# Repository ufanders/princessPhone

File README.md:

# princessPhone

TL;DR: Bluetooth adaptor for standard wired telephones. Just plug it in.

This project bridges the gap between the wired telephones we grew up with and our modern (mobile) telephones. Contains a PIC32MX1 microcontroller, RN-52 Bluetooth audio module, Silvertel AG1170 SLIC and audio support components.

=]

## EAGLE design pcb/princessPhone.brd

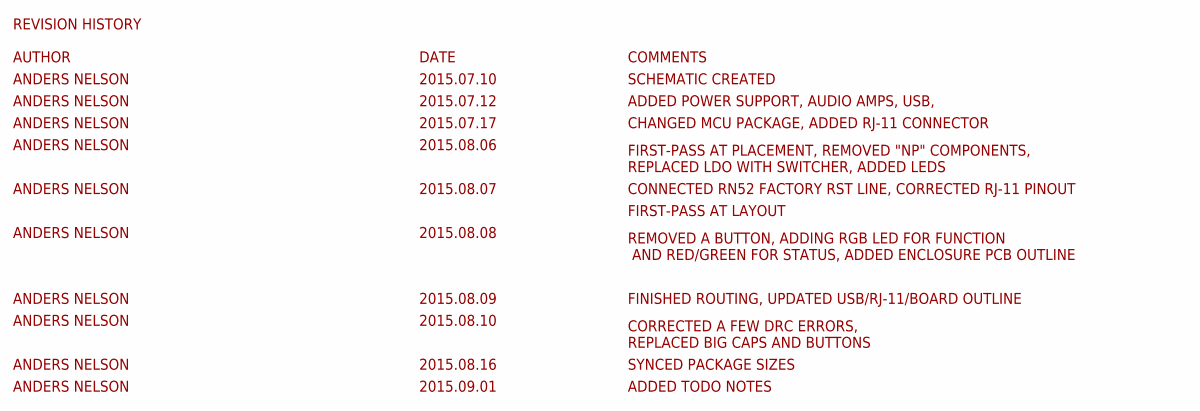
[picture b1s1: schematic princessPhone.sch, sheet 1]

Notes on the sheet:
REVISION HISTORY
AUTHOR
DATE
COMMENTS
ANDERS NELSON
2015.07.10
SCHEMATIC CREATED
2015.07.12
ADDED POWER SUPPORT, AUDIO AMPS, USB,
2015.07.17
CHANGED MCU PACKAGE, ADDED RJ-11 CONNECTOR
2015.08.06
FIRST-PASS AT PLACEMENT, REMOVED "NP" COMPONENTS, REPLACED LDO WITH SWITCHER, ADDED LEDS
2015.08.07
CONNECTED RN52 FACTORY RST LINE, CORRECTED RJ-11 PINOUT
FIRST-PASS AT LAYOUT
2015.08.08
REMOVED A BUTTON, ADDING RGB LED FOR FUNCTION AND RED/GREEN FOR STATUS, ADDED ENCLOSURE PCB OUTLINE
2015.08.09
FINISHED ROUTING, UPDATED USB/RJ-11/BOARD OUTLINE
2015.08.10
CORRECTED A FEW DRC ERRORS, REPLACED BIG CAPS AND BUTTONS
2015.08.16
SYNCED PACKAGE SIZES
2015.09.01
ADDED TODO NOTES

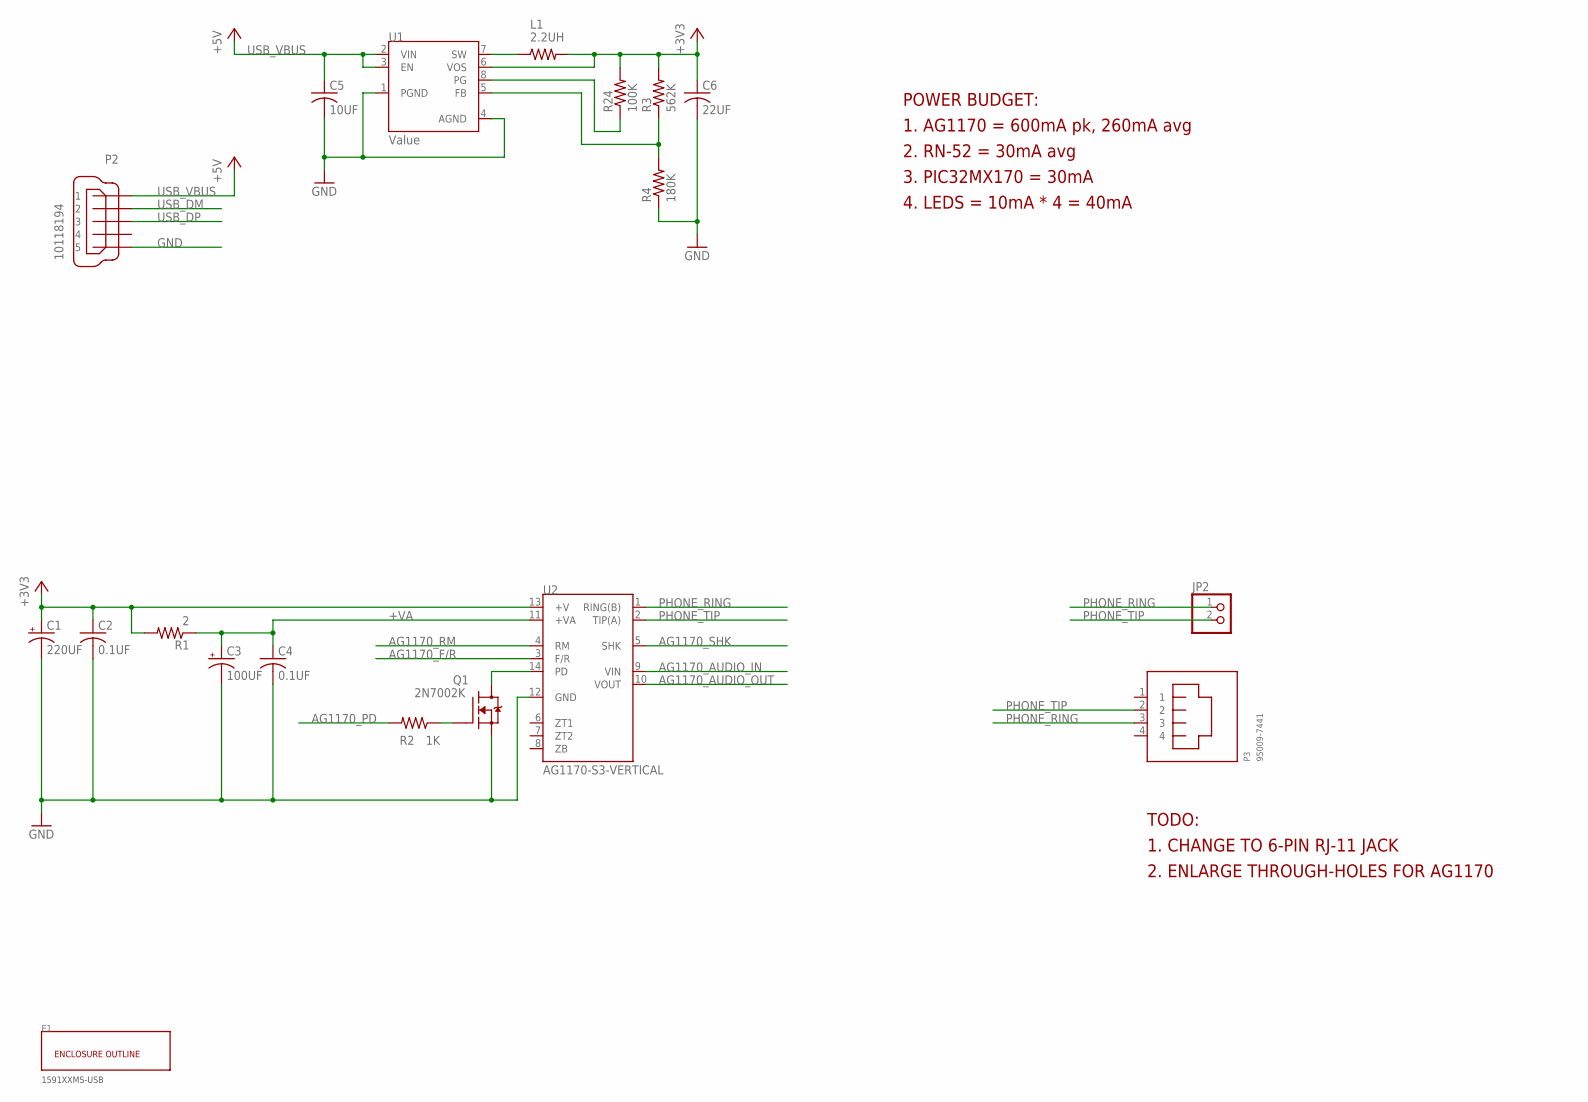
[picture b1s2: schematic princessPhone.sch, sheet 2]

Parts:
C1: 220UF; E2,5-7
C2, C4: 0.1UF; C0603
C3: 100UF; E2,5-7
C5: 10UF; C0603
C6: 22UF; C1206
E1: 1591XXMS-USB; 1591XXMSBK-USB
JP2: PINHD-1X2; 1X02
L1: 2.2UH; R0805
P2: 10118194
P3: 95009-7441
Q1: 2N7002K; SOT23
R1: 2; R0603
R2: 1K; R0603
R3: 562K; R0603
R4: 180K; R0603
R24: 100K; R0603
U1: Value; DGK0008A_N
U2: AG1170-S3-VERTICAL; AG1170X-S

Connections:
+3V3: C1.+, C2.1, C6.1, L1.2, R1.2, R3.2, R24.2, U1.6 (VOS), U2.13 (+V); also elsewhere on the board
+VA: C3.+, C4.1, R1.1, U2.11 (+VA)
AG1170_AUDIO_IN: U2.9 (VIN); also elsewhere on the board
AG1170_AUDIO_OUT: U2.10 (VOUT); also elsewhere on the board
AG1170_F/R: U2.3 (F/R); also elsewhere on the board
AG1170_PD: R2.2; also elsewhere on the board
AG1170_RM: U2.4 (RM); also elsewhere on the board
AG1170_SHK: U2.5 (SHK); also elsewhere on the board
GND: C1.-, C2.2, C3.-, C4.2, C5.2, C6.2, P2.5, Q1.2 (S), R4.1, U1.1 (PGND), U1.4 (AGND), U2.12 (GND); also elsewhere on the board
unnamed: Q1.1 (G), R2.1
unnamed: Q1.3 (D), U2.14 (PD)
unnamed: L1.1, U1.7 (SW)
unnamed: R24.1, U1.8 (PG)
unnamed: R3.1, R4.2, U1.5 (FB)
PHONE_RING: JP2.1, P3.3, U2.1 (RING(B))
PHONE_TIP: JP2.2, P3.2, U2.2 (TIP(A))
USB_DM: P2.2; also elsewhere on the board
USB_DP: P2.3; also elsewhere on the board
USB_VBUS: C5.1, P2.1, U1.2 (VIN), U1.3 (EN); also elsewhere on the board

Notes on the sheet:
POWER BUDGET:
1. AG1170 = 600mA pk, 260mA avg
2. RN-52 = 30mA avg
3. PIC32MX170 = 30mA
4. LEDS = 10mA * 4 = 40mA
TODO:
1. CHANGE TO 6-PIN RJ-11 JACK
2. ENLARGE THROUGH-HOLES FOR AG1170

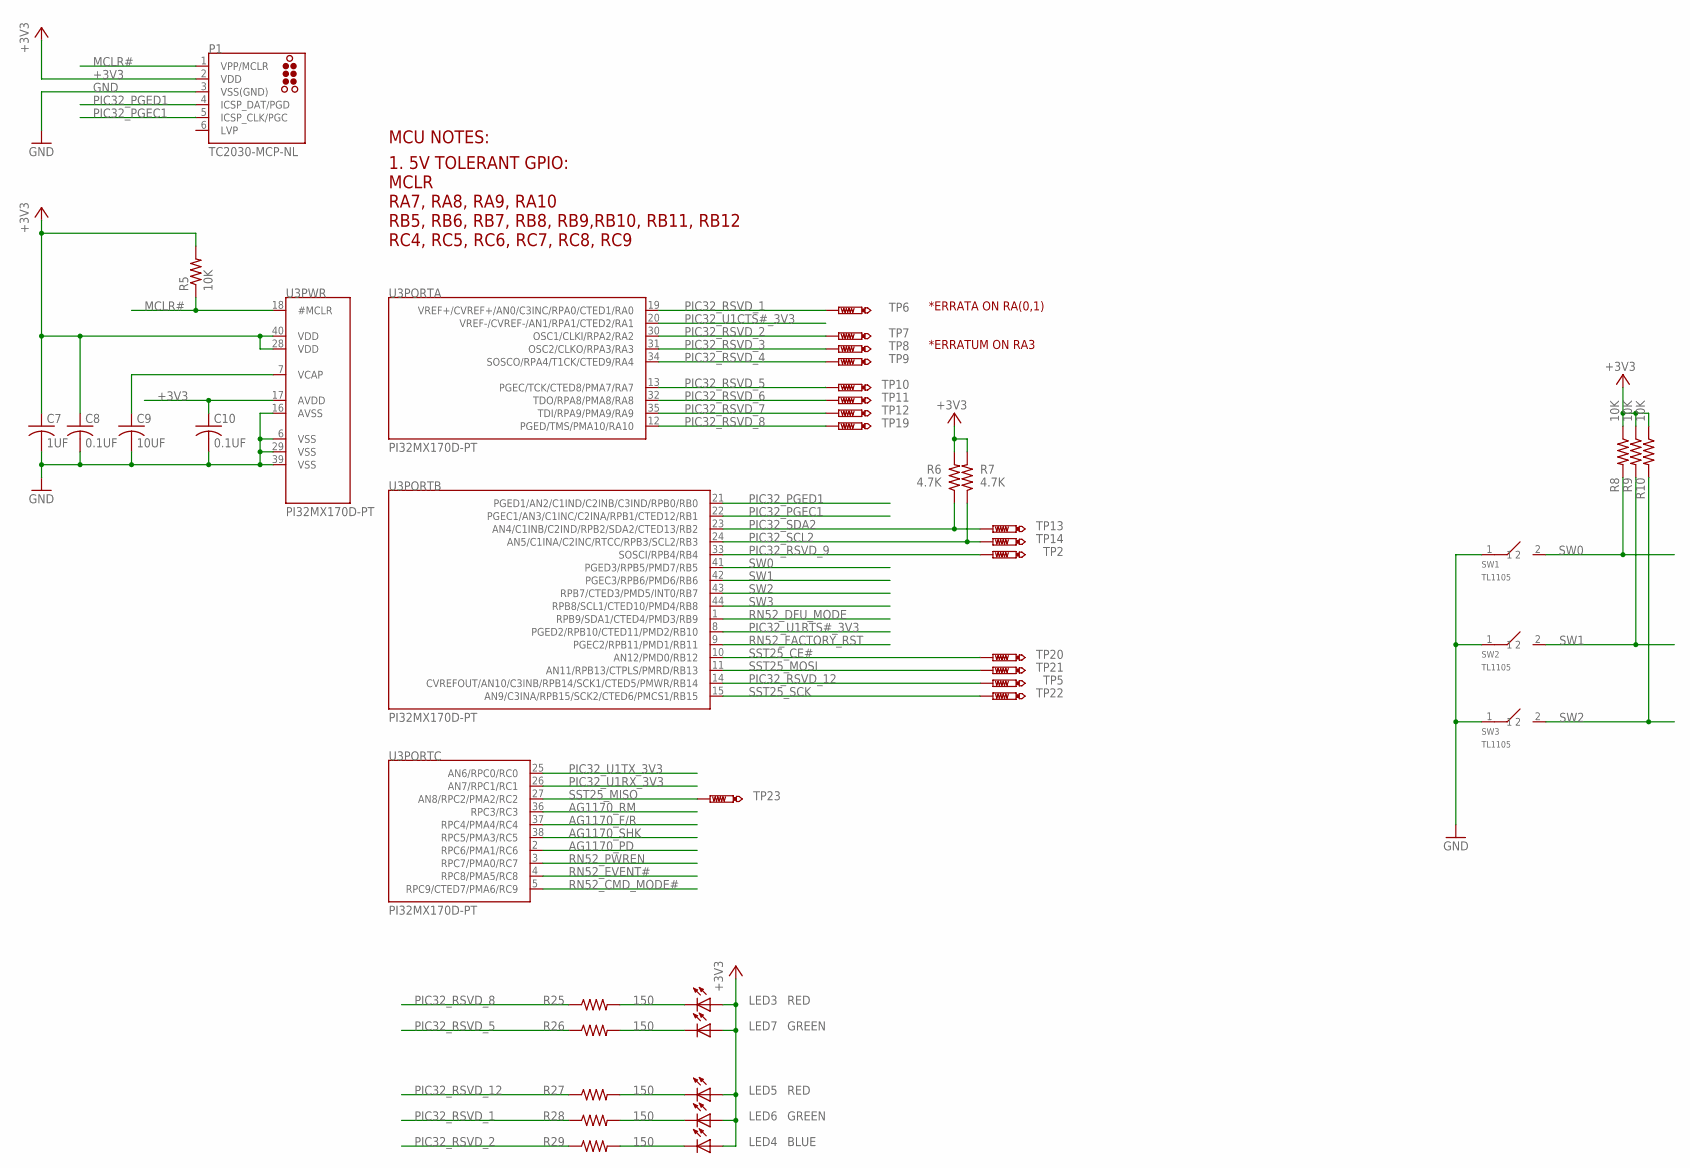
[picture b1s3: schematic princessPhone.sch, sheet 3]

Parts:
C7: 1UF; C0603
C8, C10: 0.1UF; C0603
C9: 10UF; C0603
LED3, LED5: RED; CHIPLED_0603
LED4: BLUE; CHIPLED_0603
LED6, LED7: GREEN; CHIPLED_0603
P1: TC2030-MCP-NL
R5, R8, R9, R10: 10K; R0603
R6, R7: 4.7K; R0603
R25, R26, R27, R28, R29: 150; R0603
SW1, SW2, SW3: TL1105; TL1105_RA
TP2, TP5, TP6, TP7, TP8, TP9, TP10, TP11, TP12, TP13, TP14, TP19, TP20, TP21, TP22, TP23: PTR1B1,27; B1,27
U3: PI32MX170D-PT; TQFP44

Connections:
+3V3: C7.1, C8.1, C10.1, LED3.A, LED4.A, LED5.A, LED6.A, LED7.A, P1.2 (VDD), R5.2, R6.2, R7.2, R8.1, R9.1, R10.1, U3.17 (AVDD), U3.28 (VDD), U3.40 (VDD); also elsewhere on the board
AG1170_F/R: U3.37 (RPC4/PMA4/RC4); also elsewhere on the board
AG1170_PD: U3.2 (RPC6/PMA1/RC6); also elsewhere on the board
AG1170_RM: U3.36 (RPC3/RC3); also elsewhere on the board
AG1170_SHK: U3.38 (RPC5/PMA3/RC5); also elsewhere on the board
GND: C7.2, C8.2, C9.2, C10.2, P1.3 (VSS(GND)), SW1.1, SW2.1, SW3.1, U3.6 (VSS), U3.16 (AVSS), U3.29 (VSS), U3.39 (VSS); also elsewhere on the board
MCLR#: P1.1 (VPP/MCLR), R5.1, U3.18 (#MCLR)
unnamed: LED5.C, R27.2
unnamed: C9.1, U3.7 (VCAP)
unnamed: LED3.C, R25.2
unnamed: LED7.C, R26.2
unnamed: LED6.C, R28.2
unnamed: LED4.C, R29.2
PIC32_PGEC1: P1.5 (ICSP_CLK/PGC), U3.22 (PGEC1/AN3/C1INC/C2INA/RPB1/CTED12/RB1)
PIC32_PGED1: P1.4 (ICSP_DAT/PGD), U3.21 (PGED1/AN2/C1IND/C2INB/C3IND/RPB0/RB0)
PIC32_RSVD_1: R28.1, TP6.TP, U3.19 (VREF+/CVREF+/AN0/C3INC/RPA0/CTED1/RA0)
PIC32_RSVD_2: R29.1, TP7.TP, U3.30 (OSC1/CLKI/RPA2/RA2)
PIC32_RSVD_3: TP8.TP, U3.31 (OSC2/CLKO/RPA3/RA3)
PIC32_RSVD_4: TP9.TP, U3.34 (SOSCO/RPA4/T1CK/CTED9/RA4)
PIC32_RSVD_5: R26.1, TP10.TP, U3.13 (PGEC/TCK/CTED8/PMA7/RA7)
PIC32_RSVD_6: TP11.TP, U3.32 (TDO/RPA8/PMA8/RA8)
PIC32_RSVD_7: TP12.TP, U3.35 (TDI/RPA9/PMA9/RA9)
PIC32_RSVD_8: R25.1, TP19.TP, U3.12 (PGED/TMS/PMA10/RA10)
PIC32_RSVD_9: TP2.TP, U3.33 (SOSCI/RPB4/RB4)
PIC32_RSVD_12: R27.1, TP5.TP, U3.14 (CVREFOUT/AN10/C3INB/RPB14/SCK1/CTED5/PM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)
PIC32_SCL2: R7.1, TP14.TP, U3.24 (AN5/C1INA/C2INC/RTCC/RPB3/SCL2/RB3)
PIC32_SDA2: R6.1, TP13.TP, U3.23 (AN4/C1INB/C2IND/RPB2/SDA2/CTED13/RB2)
PIC32_U1CTS#_3V3: U3.20 (VREF-/CVREF-/AN1/RPA1/CTED2/RA1); also elsewhere on the board
PIC32_U1RTS#_3V3: U3.8 (PGED2/RPB10/CTED11/PMD2/RB10); also elsewhere on the board
PIC32_U1RX_3V3: U3.26 (AN7/RPC1/RC1); also elsewhere on the board
PIC32_U1TX_3V3: U3.25 (AN6/RPC0/RC0); also elsewhere on the board
RN52_CMD_MODE#: U3.5 (RPC9/CTED7/PMA6/RC9); also elsewhere on the board
RN52_DFU_MODE: U3.1 (RPB9/SDA1/CTED4/PMD3/RB9); also elsewhere on the board
RN52_EVENT#: U3.4 (RPC8/PMA5/RC8); also elsewhere on the board
RN52_FACTORY_RST: U3.9 (PGEC2/RPB11/PMD1/RB11); also elsewhere on the board
RN52_PWREN: U3.3 (RPC7/PMA0/RC7); also elsewhere on the board
SST25_CE#: TP20.TP, U3.10 (AN12/PMD0/RB12)
SST25_MISO: TP23.TP, U3.27 (AN8/RPC2/PMA2/RC2)
SST25_MOSI: TP21.TP, U3.11 (AN11/RPB13/CTPLS/PMRD/RB13)
SST25_SCK: TP22.TP, U3.15 (AN9/C3INA/RPB15/SCK2/CTED6/PMCS1/RB15)
SW0: R8.2, SW1.2, U3.41 (PGED3/RPB5/PMD7/RB5)
SW1: R9.2, SW2.2, U3.42 (PGEC3/RPB6/PMD6/RB6)
SW2: R10.2, SW3.2, U3.43 (RPB7/CTED3/PMD5/INT0/RB7)
SW3: U3.44 (RPB8/SCL1/CTED10/PMD4/RB8)

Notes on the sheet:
*ERRATUM ON RA3
1. 5V TOLERANT GPIO: MCLR RA7, RA8, RA9, RA10 RB5, RB6, RB7, RB8, RB9,RB10, RB11, RB12 RC4, RC5, RC6, RC7, RC8, RC9
*ERRATA ON RA(0,1)
MCU NOTES:

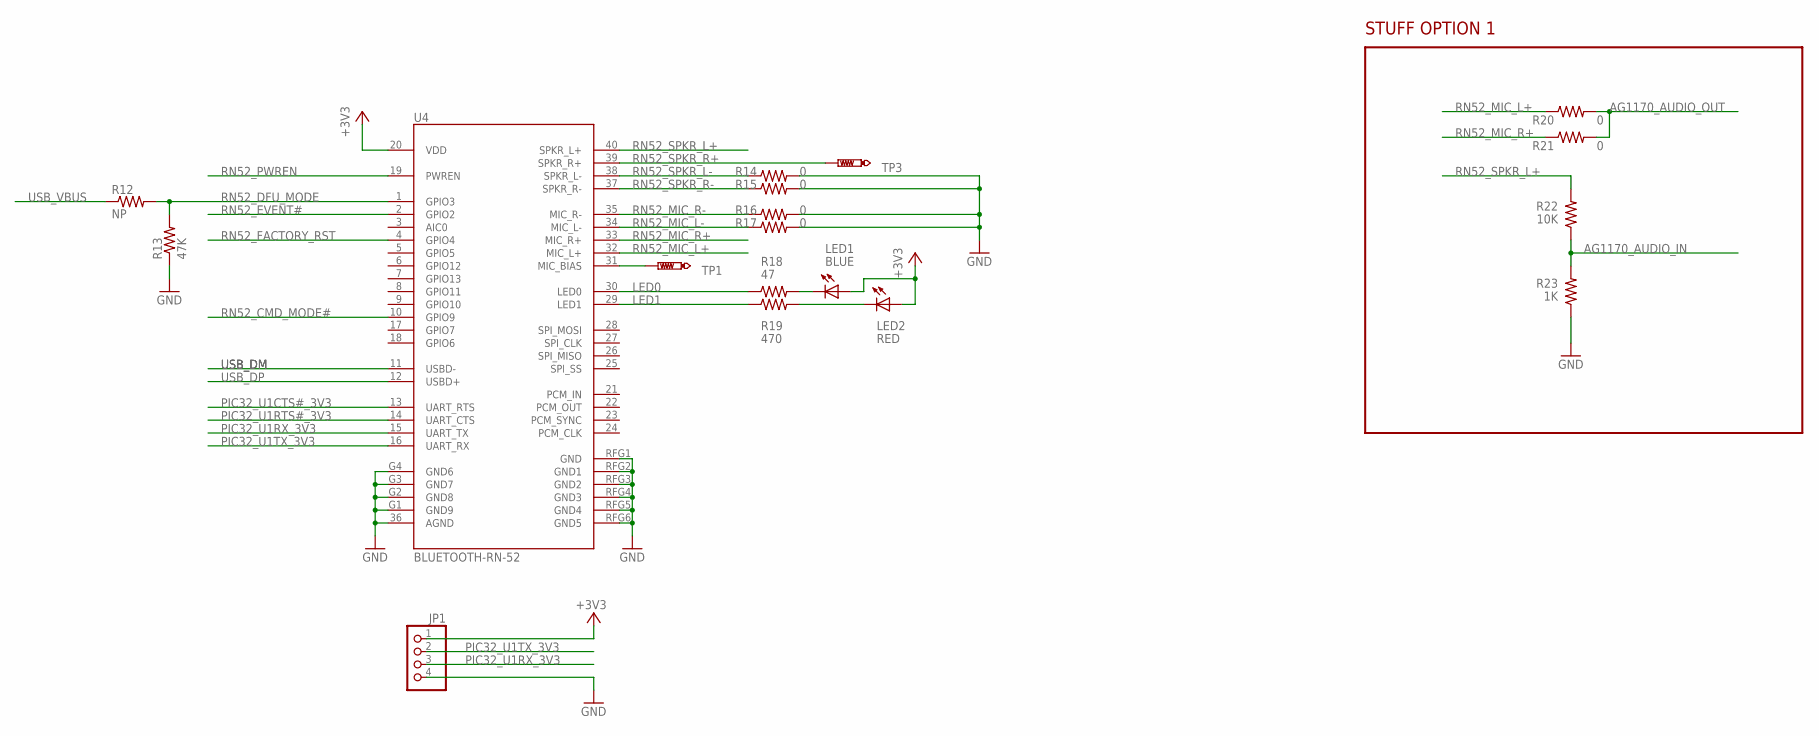
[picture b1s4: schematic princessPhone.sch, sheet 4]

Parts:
JP1: PINHD-1X4; 1X04
LED1: BLUE; CHIPLED_0603
LED2: RED; CHIPLED_0603
R12: NP; R0603
R13: 47K; R0603
R14, R15, R16, R17, R20, R21: 0; R0603
R18: 47; R0603
R19: 470; R0603
R22: 10K; R0603
R23: 1K; R0603
TP1, TP3: PTR1B1,27; B1,27
U4: BLUETOOTH-RN-52; RN-52

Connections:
+3V3: JP1.1, LED1.A, LED2.A, U4.20 (VDD); also elsewhere on the board
AG1170_AUDIO_IN: R22.1, R23.2; also elsewhere on the board
AG1170_AUDIO_OUT: R20.2, R21.2; also elsewhere on the board
GND: JP1.4, R13.1, R14.2, R15.2, R16.2, R17.2, R23.1, U4.36 (AGND), U4.G1 (GND9), U4.G2 (GND8), U4.G3 (GND7), U4.G4 (GND6), U4.RFG1 (GND), U4.RFG2 (GND1), U4.RFG3 (GND2), U4.RFG4 (GND3), U4.RFG5 (GND4), U4.RFG6 (GND5); also elsewhere on the board
LED0: R18.1, U4.30 (LED0)
LED1: R19.1, U4.29 (LED1)
unnamed: LED1.C, R18.2
unnamed: LED2.C, R19.2
unnamed: TP1.TP, U4.31 (MIC_BIAS)
PIC32_U1CTS#_3V3: U4.13 (UART_RTS); also elsewhere on the board
PIC32_U1RTS#_3V3: U4.14 (UART_CTS); also elsewhere on the board
PIC32_U1RX_3V3: JP1.3, U4.15 (UART_TX); also elsewhere on the board
PIC32_U1TX_3V3: JP1.2, U4.16 (UART_RX); also elsewhere on the board
RN52_CMD_MODE#: U4.10 (GPIO9); also elsewhere on the board
RN52_DFU_MODE: R12.2, R13.2, U4.1 (GPIO3); also elsewhere on the board
RN52_EVENT#: U4.2 (GPIO2); also elsewhere on the board
RN52_FACTORY_RST: U4.4 (GPIO4); also elsewhere on the board
RN52_MIC_L+: R20.1, U4.32 (MIC_L+)
RN52_MIC_L-: R17.1, U4.34 (MIC_L-)
RN52_MIC_R+: R21.1, U4.33 (MIC_R+)
RN52_MIC_R-: R16.1, U4.35 (MIC_R-)
RN52_PWREN: U4.19 (PWREN); also elsewhere on the board
RN52_SPKR_L+: R22.2, U4.40 (SPKR_L+)
RN52_SPKR_L-: R14.1, U4.38 (SPKR_L-)
RN52_SPKR_R+: TP3.TP, U4.39 (SPKR_R+)
RN52_SPKR_R-: R15.1, U4.37 (SPKR_R-)
USB_DM: U4.11 (USBD-); also elsewhere on the board
USB_DP: U4.12 (USBD+); also elsewhere on the board
USB_VBUS: R12.1; also elsewhere on the board

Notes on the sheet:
STUFF OPTION 1

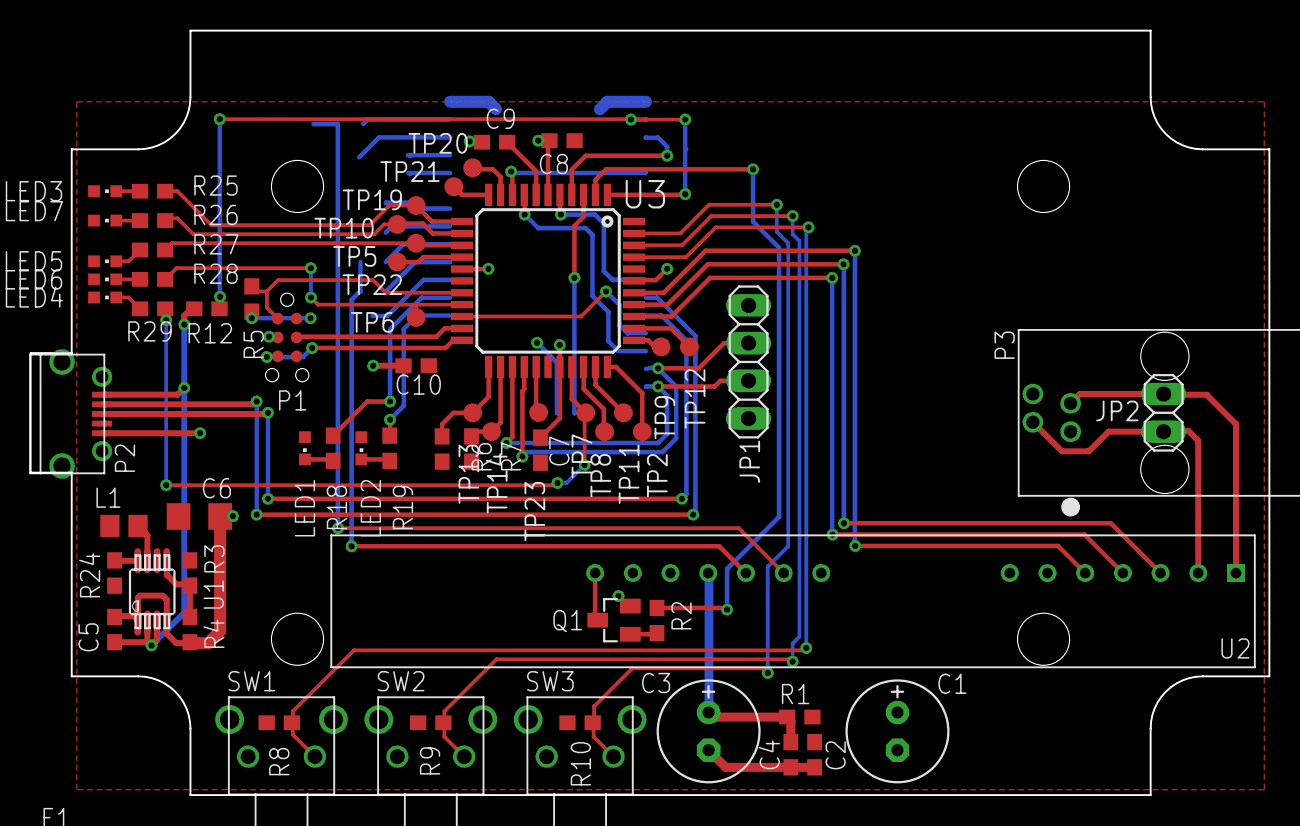
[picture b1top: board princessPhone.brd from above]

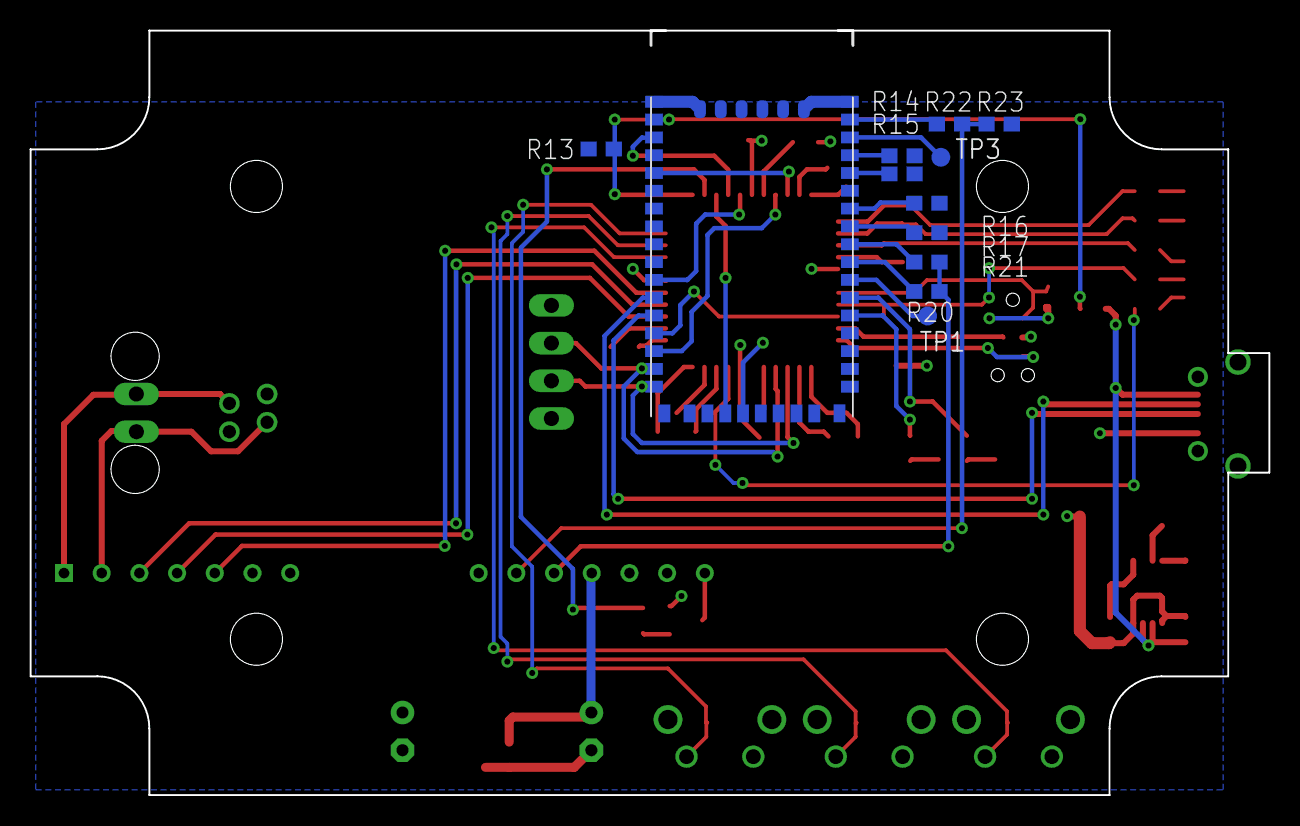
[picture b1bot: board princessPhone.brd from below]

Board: 2 copper layers, 83.5 x 51.5 mm, 78 parts (12 on the bottom side), 69 nets.

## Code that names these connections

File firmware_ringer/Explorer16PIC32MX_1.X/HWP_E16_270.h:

#ifndef HWP_E16_270_H
#define HWP_E16_270_H

#define VERSION_HARDWARE_MAJOR 'E'
#define VERSION_HARDWARE_MINOR 16

// Set configuration fuses (but only in Main.c where SET_CONFIG_FUSES is defined)
#if defined(SET_CONFIG_FUSES)

    //PROVIDES 48MHZ FCY
    #pragma config FPLLMUL  = MUL_24        // PLL Multiplier
    #pragma config FPLLIDIV = DIV_2          // PLL Input Divider
    #pragma config FPLLODIV = DIV_2     // PLL Output Divider
    #pragma config FPBDIV   = DIV_1         // Peripheral Clock divisor
    #pragma config WDTPS    = PS1           // Watchdog Timer Postscale
    #pragma config FCKSM    = CSDCMD        // Clock Switching & Fail Safe Clock Monitor
    #pragma config OSCIOFNC = OFF           // CLKO Enable
    #pragma config POSCMOD  = HS            // Primary Oscillator
    #pragma config IESO     = OFF           // Internal/External Switch-over
    #pragma config FSOSCEN  = ON           // Secondary Oscillator Enable
    #pragma config FNOSC    = PRIPLL        // Oscillator Selection

    #ifdef __DEBUG
        #pragma config CP       = OFF       // Code Protect
        #pragma config FWDTEN   = OFF       // Watchdog Timer
    #else
        #pragma config CP       = OFF        // Code Protect
        #pragma config FWDTEN   = OFF        // Watchdog Timer
    #endif

    #pragma config BWP      = OFF           // Boot Flash Write Protect
    #pragma config PWP      = OFF           // Program Flash Write Protect
    #pragma config ICESEL   = ICS_PGx2      // ICE/ICD Comm Channel Select
    #pragma config DEBUG    = ON            // Background Debugger Enable
    #pragma config FUSBIDIO = OFF
    #pragma config FVBUSONIO = OFF

#endif

// Clock frequency values
// These directly influence timed events using the Tick module.  They also are used for UART and SPI baud rate generation.
#define GetSystemClock()	(48000000ul)		// Hz
#define GetInstructionClock()	(GetSystemClock()/1)	// Normally GetSystemClock()/4 for PIC18, GetSystemClock()/2 for PIC24/dsPIC, and GetSystemClock()/1 for PIC32.  Might need changing if using Doze modes.
#define GetPeripheralClock()	(GetSystemClock()/1)	// Normally GetSystemClock()/4 for PIC18, GetSystemClock()/2 for PIC24/dsPIC, and GetSystemClock()/1 for PIC32.  Divisor may be different if using a PIC32 since it's configurable.
#define SYS_FREQ GetSystemClock()
#define PB_DIV 1

// Hardware I/O pin mappings
//UART
#define UART_RX_TRIS TRISCbits.TRISC1 //RB10 on riser card
#define UART_TX_TRIS TRISCbits.TRISC0 //RB11 on riser card
#define UART_RTS_TRIS TRISBbits.TRISB10 //RGO on riser card
#define UART_CTS_TRIS TRISAbits.TRISA1 //RE6on riser card
#define UART_RX_PPS 0b0110
#define UART_TX_PPS 0b0001
#define UART_RTS_PPS 0b0010
#define UART_CTS_PPS 0b0000

//AG1170 CONTROL LINES
#define AG1170_RM_TRIS TRISCbits.TRISC3 //RG13 on riser card
#define AG1170_FR_TRIS TRISCbits.TRISC4 //RG14 on riser card
#define AG1170_SHK_TRIS TRISCbits.TRISC5 //RG15 on riser card
#define AG1170_PD_TRIS TRISCbits.TRISC6
#define AG1170_RM_LAT LATCbits.LATC3 //RG13 on riser card
#define AG1170_FR_LAT LATCbits.LATC4 //RG14 on riser card
#define AG1170_SHK_LAT LATCbits.LATC5 //RG15 on riser card
#define AG1170_PD_LAT LATCbits.LATC6
#define AG1170_RM_PORT PORTCbits.RC3 //RG13 on riser card
#define AG1170_FR_PORT PORTCbits.RC4 //RG14 on riser card
#define AG1170_SHK_PORT PORTCbits.RC5 //RG15 on riser card
#define AG1170_PD_PORT PORTCbits.RC6

//MCU AUDIO LINES
#define PWM_TRIS TRISBbits.TRISB4
#define PWM_PPS 0b0101


//RN52 CONTROL LINES
#define RN52_DFU_MODE_TRIS TRISBbits.TRISB9
#define RN52_FACTORY_RST_TRIS TRISBbits.TRISB11
#define RN52_PWREN_TRIS TRISCbits.TRISC7
#define RN52_EVENT_L_TRIS TRISCbits.TRISC8
#define RN52_CMD_MODE_L_TRIS TRISCbits.TRISC9
#define RN52_DFU_MODE_LAT LATBbits.LATB9
#define RN52_FACTORY_RST_LAT LATBbits.LATB11
#define RN52_PWREN_LAT LATCbits.LATC7
#define RN52_EVENT_L_LAT LATCbits.LATC8
#define RN52_CMD_MODE_L_LAT LATCbits.LATC9
#define RN52_EVENT_L_PORT PORTCBits.RC8

//LEDS
#define LED_RED_TRIS TRISAbits.TRISA10
#define LED_GRN_TRIS TRISAbits.TRISA7
#define LED_RGB_RED_TRIS TRISBbits.TRISB14
#define LED_RGB_GRN_TRIS TRISAbits.TRISA0
#define LED_RGB_BLU_TRIS TRISAbits.TRISA2
#define LED_RED_LAT LATAbits.LATA10
#define LED_GRN_LAT LATAbits.LATA7
#define LED_RGB_RED_LAT LATBbits.LATB14
#define LED_RGB_GRN_LAT LATAbits.LATA0
#define LED_RGB_BLU_LAT LATAbits.LATA2

//BUTTONS
#define SW0_TRIS TRISBbits.TRISB5 //RG13 on riser card
#define SW0_PORT PORTBbits.RB5
#define SW0_PU CNPUBbits.CNPUB5
#define SW1_TRIS TRISBbits.TRISB6 //RG13 on riser card
#define SW1_PORT PORTBbits.RB6
#define SW1_PU CNPUBbits.CNPUB6
#define SW2_TRIS TRISBbits.TRISB7 //RG13 on riser card
#define SW2_PORT PORTBbits.RB7
#define SW2_PU CNPUBbits.CNPUB7
        
//SPI
#define SPI_SCK_TRIS TRISBbits.TRISB15 //RC2 on riser card
#define SPI_MOSI_TRIS TRISBbits.TRISB13 //RG14 on riser card
#define SPI_MISO_TRIS TRISCbits.TRISC2 //RG14 on riser card
#define SPI_CS_TRIS TRISBbits.TRISB12 //RE5 on riser card
#define SPI_SCK_LAT LATBbits.LATB15
#define SPI_MOSI_LAT LATBbits.LATB13
#define SPI_MISO_LAT LATCbits.LATC2 //RG14 on riser card
#define SPI_CS_LAT LATBbits.LATB12
#define SPI_SCK_PPS RPB15R
#define SPI_MOSI_PPS RPB15R
#define SPI_MISO_PPS RPB15R

//I2C
#define I2C2_SDA_TRIS TRISBbits.TRISB2 //RC2 on riser card
#define I2C2_SCL_TRIS TRISBbits.TRISB3 //RG14 on riser card

#endif	/* HWP_E16_270_H */

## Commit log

2015-07-10 Created schematic. -Added SLIC to library. -Added scope grabs to doc.
2015-07-13 Added power, audio, usb.
2015-07-17 -Changed MCU package -Added RJ-11 connector
2015-07-25 -Added to library -Added line-level components -Cleaned up schematic
2015-08-07 Replaced leo with switcher, finished first-pass layout, added LEDs.
2015-08-07 gitignore
2015-08-08 FIRST PASS AT LAYOUT
2015-08-09 REMOVED BTN, ADDING LEDS, ADDED OUTLINE
2015-08-09 FINISHED ROUTING
2015-08-10 UPDATED USB/RJ-11/OUTLINE
2015-08-11 Replaced placeholder components with proper ones.
2015-08-17 Synced package sizes.
2015-08-28 gitignore, FreeRTOS firmware base.
2015-08-31 Program is running, serials still not working.
2015-09-01 Program runs, UART works but init clobbers timer system.
2016-03-28 Tried in vain to get RTOS version to work.
2016-03-28 -gitignore -Filled in hardware profile and POTS functions.
2016-03-28 Post-fab PCB tweaks.
2016-03-28 Added DTMF generator.
2016-03-31 Filled in more stuff!
2016-08-12 Continued filling in functions. -Serial port still doesn't work.

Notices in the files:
parts and their libraries:
raveGearControl: ©2009 ROFA.cz
SparkFun-RF: Licensing: Creative Commons ShareAlike 4.0 International - https://creativecommons.org/licenses/by-sa/4.0
